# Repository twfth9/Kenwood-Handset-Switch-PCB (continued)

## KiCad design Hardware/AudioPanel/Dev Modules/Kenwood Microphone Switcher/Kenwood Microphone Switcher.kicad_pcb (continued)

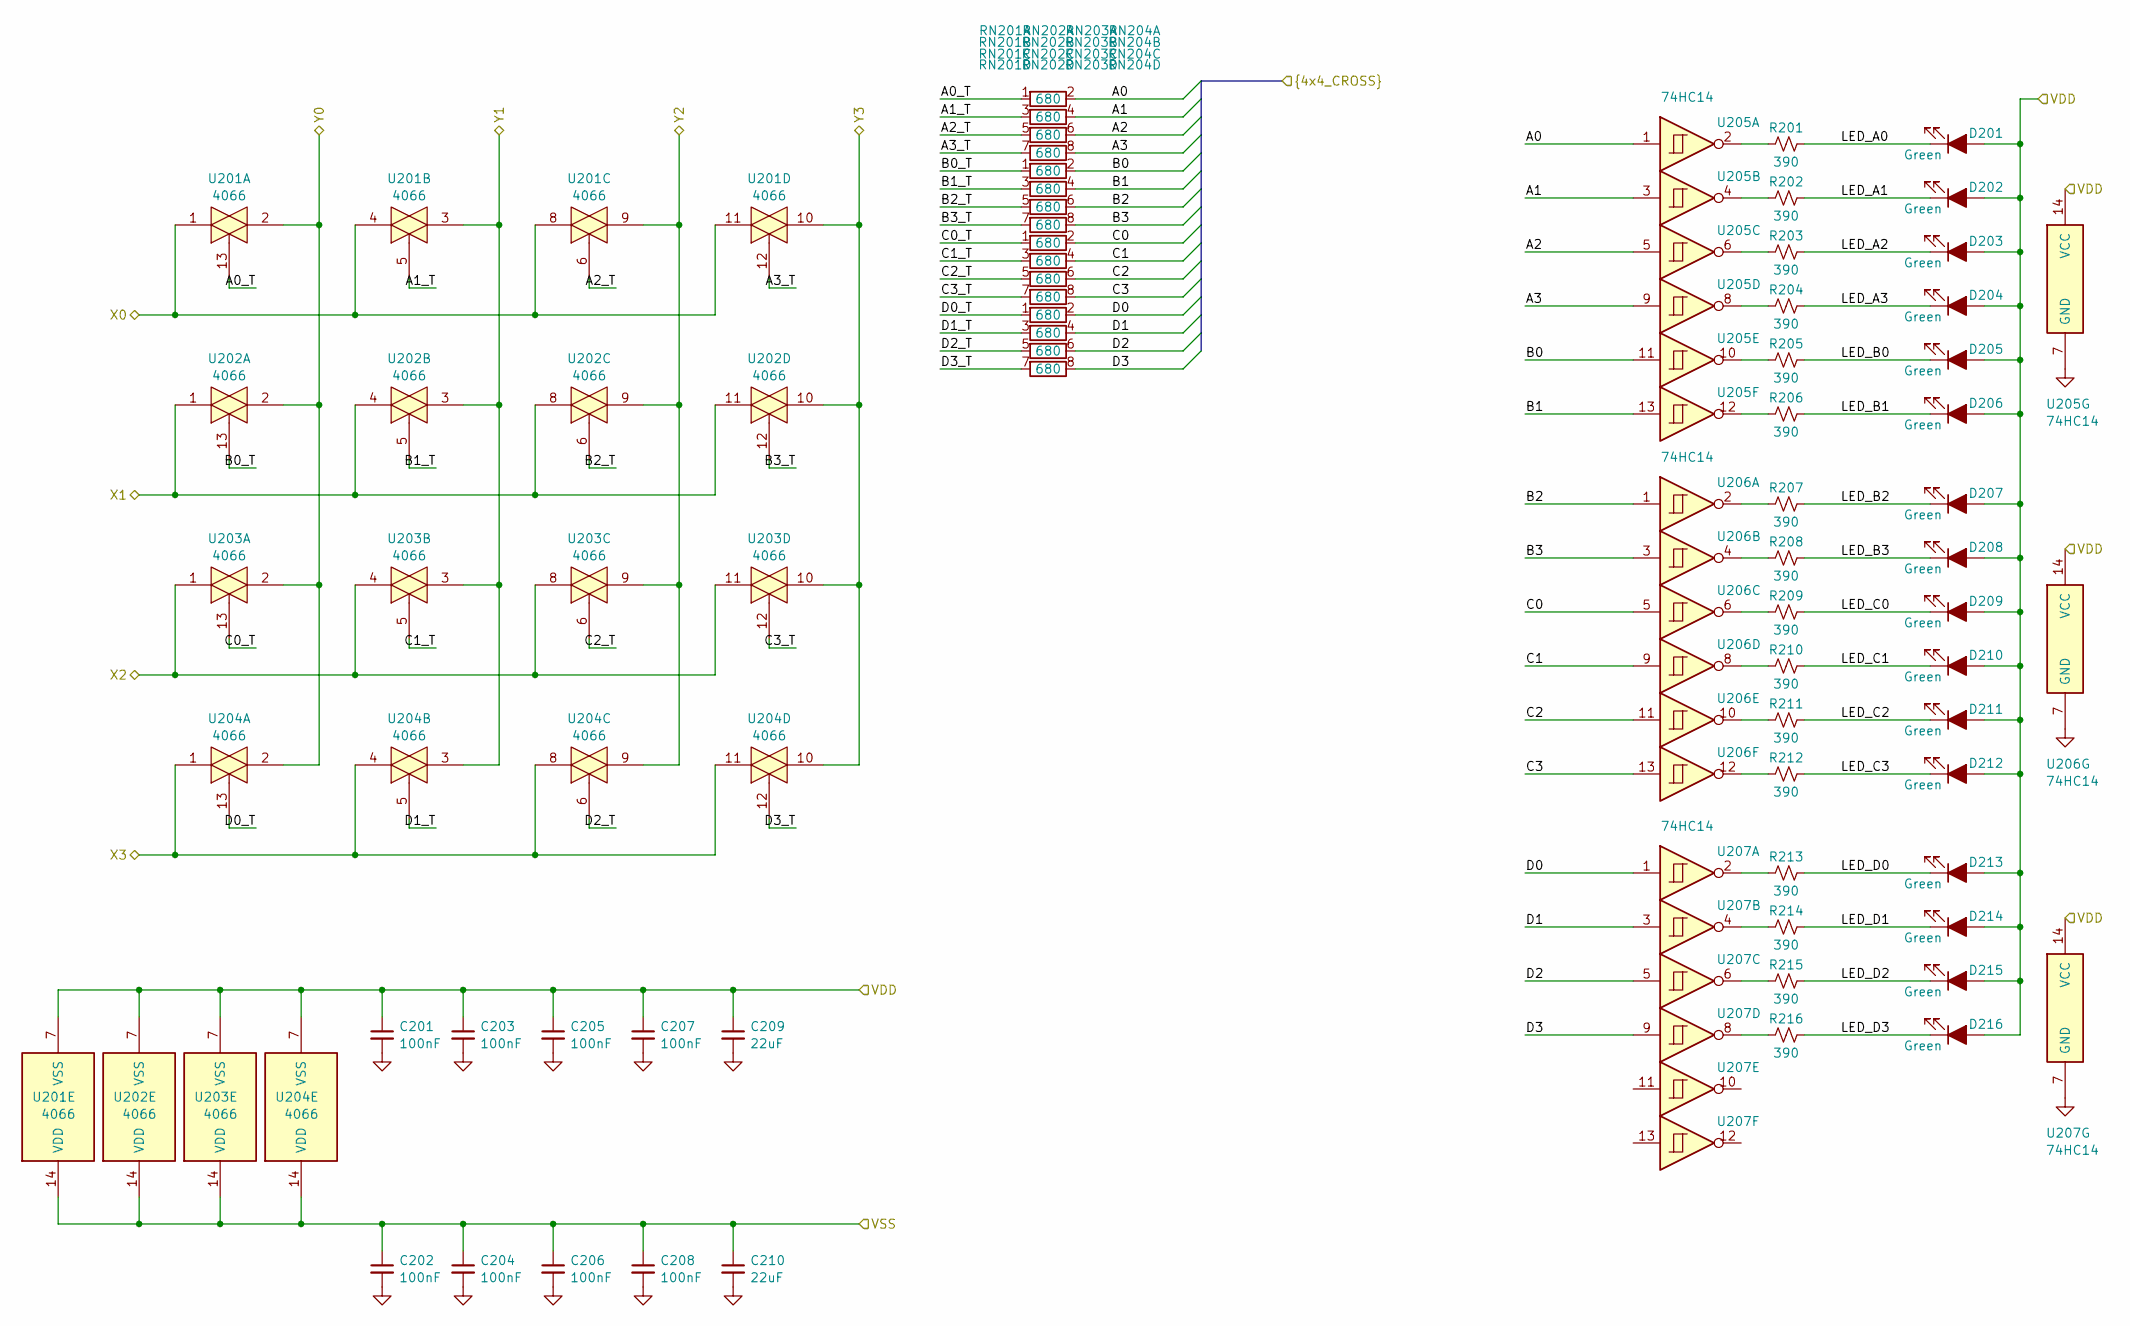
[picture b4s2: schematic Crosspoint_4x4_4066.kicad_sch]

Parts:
C201, C202, C203, C204, C205, C206, C207, C208: 100nF; C_0402_1005Metric
C209, C210: 22uF; C_0603_1608Metric
D201, D202, D203, D204, D205, D206, D207, D208, D209, D210, D211, D212, D213, D214, D215, D216: Green; LED_0603_1608Metric; DigiKey Part Number 732-5016-ND
R201, R202, R203, R204, R205, R206, R207, R208, R209, R210, R211, R212, R213, R214, R215, R216: 390; R_0402_1005Metric
RN201, RN202, RN203, RN204: 680; R_Array_Convex_4x1206
U201, U202, U203, U204: 4066; SOIC-14_3.9x8.7mm_P1.27mm
U205, U206, U207: 74HC14; SOIC-14_3.9x8.7mm_P1.27mm

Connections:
/4x4 Crosspoint Switch/A0: RN201.2, U205.1; also elsewhere on the board
/4x4 Crosspoint Switch/A0_T: RN201.1, U201.13
/4x4 Crosspoint Switch/A1: RN201.4, U205.3; also elsewhere on the board
/4x4 Crosspoint Switch/A1_T: RN201.3, U201.5
/4x4 Crosspoint Switch/A2: RN201.6, U205.5; also elsewhere on the board
/4x4 Crosspoint Switch/A2_T: RN201.5, U201.6
/4x4 Crosspoint Switch/A3: RN201.8, U205.9; also elsewhere on the board
/4x4 Crosspoint Switch/A3_T: RN201.7, U201.12
/4x4 Crosspoint Switch/B0: RN202.2, U205.11; also elsewhere on the board
/4x4 Crosspoint Switch/B0_T: RN202.1, U202.13
/4x4 Crosspoint Switch/B1: RN202.4, U205.13; also elsewhere on the board
/4x4 Crosspoint Switch/B1_T: RN202.3, U202.5
/4x4 Crosspoint Switch/B2: RN202.6, U206.1; also elsewhere on the board
/4x4 Crosspoint Switch/B2_T: RN202.5, U202.6
/4x4 Crosspoint Switch/B3: RN202.8, U206.3; also elsewhere on the board
/4x4 Crosspoint Switch/B3_T: RN202.7, U202.12
/4x4 Crosspoint Switch/C0: RN203.2, U206.5; also elsewhere on the board
/4x4 Crosspoint Switch/C0_T: RN203.1, U203.13
/4x4 Crosspoint Switch/C1: RN203.4, U206.9; also elsewhere on the board
/4x4 Crosspoint Switch/C1_T: RN203.3, U203.5
/4x4 Crosspoint Switch/C2: RN203.6, U206.11; also elsewhere on the board
/4x4 Crosspoint Switch/C2_T: RN203.5, U203.6
/4x4 Crosspoint Switch/C3: RN203.8, U206.13; also elsewhere on the board
/4x4 Crosspoint Switch/C3_T: RN203.7, U203.12
/4x4 Crosspoint Switch/D0: RN204.2, U207.1; also elsewhere on the board
/4x4 Crosspoint Switch/D0_T: RN204.1, U204.13
/4x4 Crosspoint Switch/D1: RN204.4, U207.3; also elsewhere on the board
/4x4 Crosspoint Switch/D1_T: RN204.3, U204.5
/4x4 Crosspoint Switch/D2: RN204.6, U207.5; also elsewhere on the board
/4x4 Crosspoint Switch/D2_T: RN204.5, U204.6
/4x4 Crosspoint Switch/D3: RN204.8, U207.9; also elsewhere on the board
/4x4 Crosspoint Switch/D3_T: RN204.7, U204.12
/4x4 Crosspoint Switch/LED_A0: D201.1 (K), R201.1
/4x4 Crosspoint Switch/LED_A1: D202.1 (K), R202.1
/4x4 Crosspoint Switch/LED_A2: D203.1 (K), R203.1
/4x4 Crosspoint Switch/LED_A3: D204.1 (K), R204.1
/4x4 Crosspoint Switch/LED_B0: D205.1 (K), R205.1
/4x4 Crosspoint Switch/LED_B1: D206.1 (K), R206.1
/4x4 Crosspoint Switch/LED_B2: D207.1 (K), R207.1
/4x4 Crosspoint Switch/LED_B3: D208.1 (K), R208.1
/4x4 Crosspoint Switch/LED_C0: D209.1 (K), R209.1
/4x4 Crosspoint Switch/LED_C1: D210.1 (K), R210.1
/4x4 Crosspoint Switch/LED_C2: D211.1 (K), R211.1
/4x4 Crosspoint Switch/LED_C3: D212.1 (K), R212.1
/4x4 Crosspoint Switch/LED_D0: D213.1 (K), R213.1
/4x4 Crosspoint Switch/LED_D1: D214.1 (K), R214.1
/4x4 Crosspoint Switch/LED_D2: D215.1 (K), R215.1
/4x4 Crosspoint Switch/LED_D3: D216.1 (K), R216.1
/480_MIC.MIC: U201.1, U201.4, U201.8, U201.11; also elsewhere on the board
/700_MIC.MIC: U203.1, U203.4, U203.8, U203.11; also elsewhere on the board
/710_MIC.MIC: U202.1, U202.4, U202.8, U202.11; also elsewhere on the board
/+5V_CROSSPOINT: C201.1, C203.1, C205.1, C207.1, C209.1, D201.2 (A), D202.2 (A), D203.2 (A), D204.2 (A), D205.2 (A), D206.2 (A), D207.2 (A), D208.2 (A), D209.2 (A), D210.2 (A), D211.2 (A), D212.2 (A), D213.2 (A), D214.2 (A), D215.2 (A), D216.2 (A), U201.7 (VSS), U202.7 (VSS), U203.7 (VSS), U204.7 (VSS), U205.14 (VCC), U206.14 (VCC), U207.14 (VCC); also elsewhere on the board
/CODRIVER_MIC.MIC: U201.3, U202.3, U203.3, U204.3; also elsewhere on the board
/CROSSMIC_A: U201.9, U202.9, U203.9, U204.9; also elsewhere on the board
/CROSSMIC_B: U201.10, U202.10, U203.10, U204.10; also elsewhere on the board
/DRIVER_MIC.MIC: U201.2, U202.2, U203.2, U204.2; also elsewhere on the board
/EXTRA_MIC.MIC: U204.1, U204.4, U204.8, U204.11; also elsewhere on the board
/VSS_CROSSPOINT: C202.1, C204.1, C206.1, C208.1, C210.1, U201.14 (VDD), U202.14 (VDD), U203.14 (VDD), U204.14 (VDD); also elsewhere on the board
GND: C201.2, C202.2, C203.2, C204.2, C205.2, C206.2, C207.2, C208.2, C209.2, C210.2, U205.7 (GND), U206.7 (GND), U207.7 (GND); also elsewhere on the board
unnamed: R201.2, U205.2
unnamed: R202.2, U205.4
unnamed: R203.2, U205.6
unnamed: R204.2, U205.8
unnamed: R205.2, U205.10
unnamed: R206.2, U205.12
unnamed: R207.2, U206.2
unnamed: R208.2, U206.4
unnamed: R209.2, U206.6
unnamed: R210.2, U206.8
unnamed: R211.2, U206.10
unnamed: R212.2, U206.12
unnamed: R213.2, U207.2
unnamed: R214.2, U207.4
unnamed: R215.2, U207.6
unnamed: R216.2, U207.8

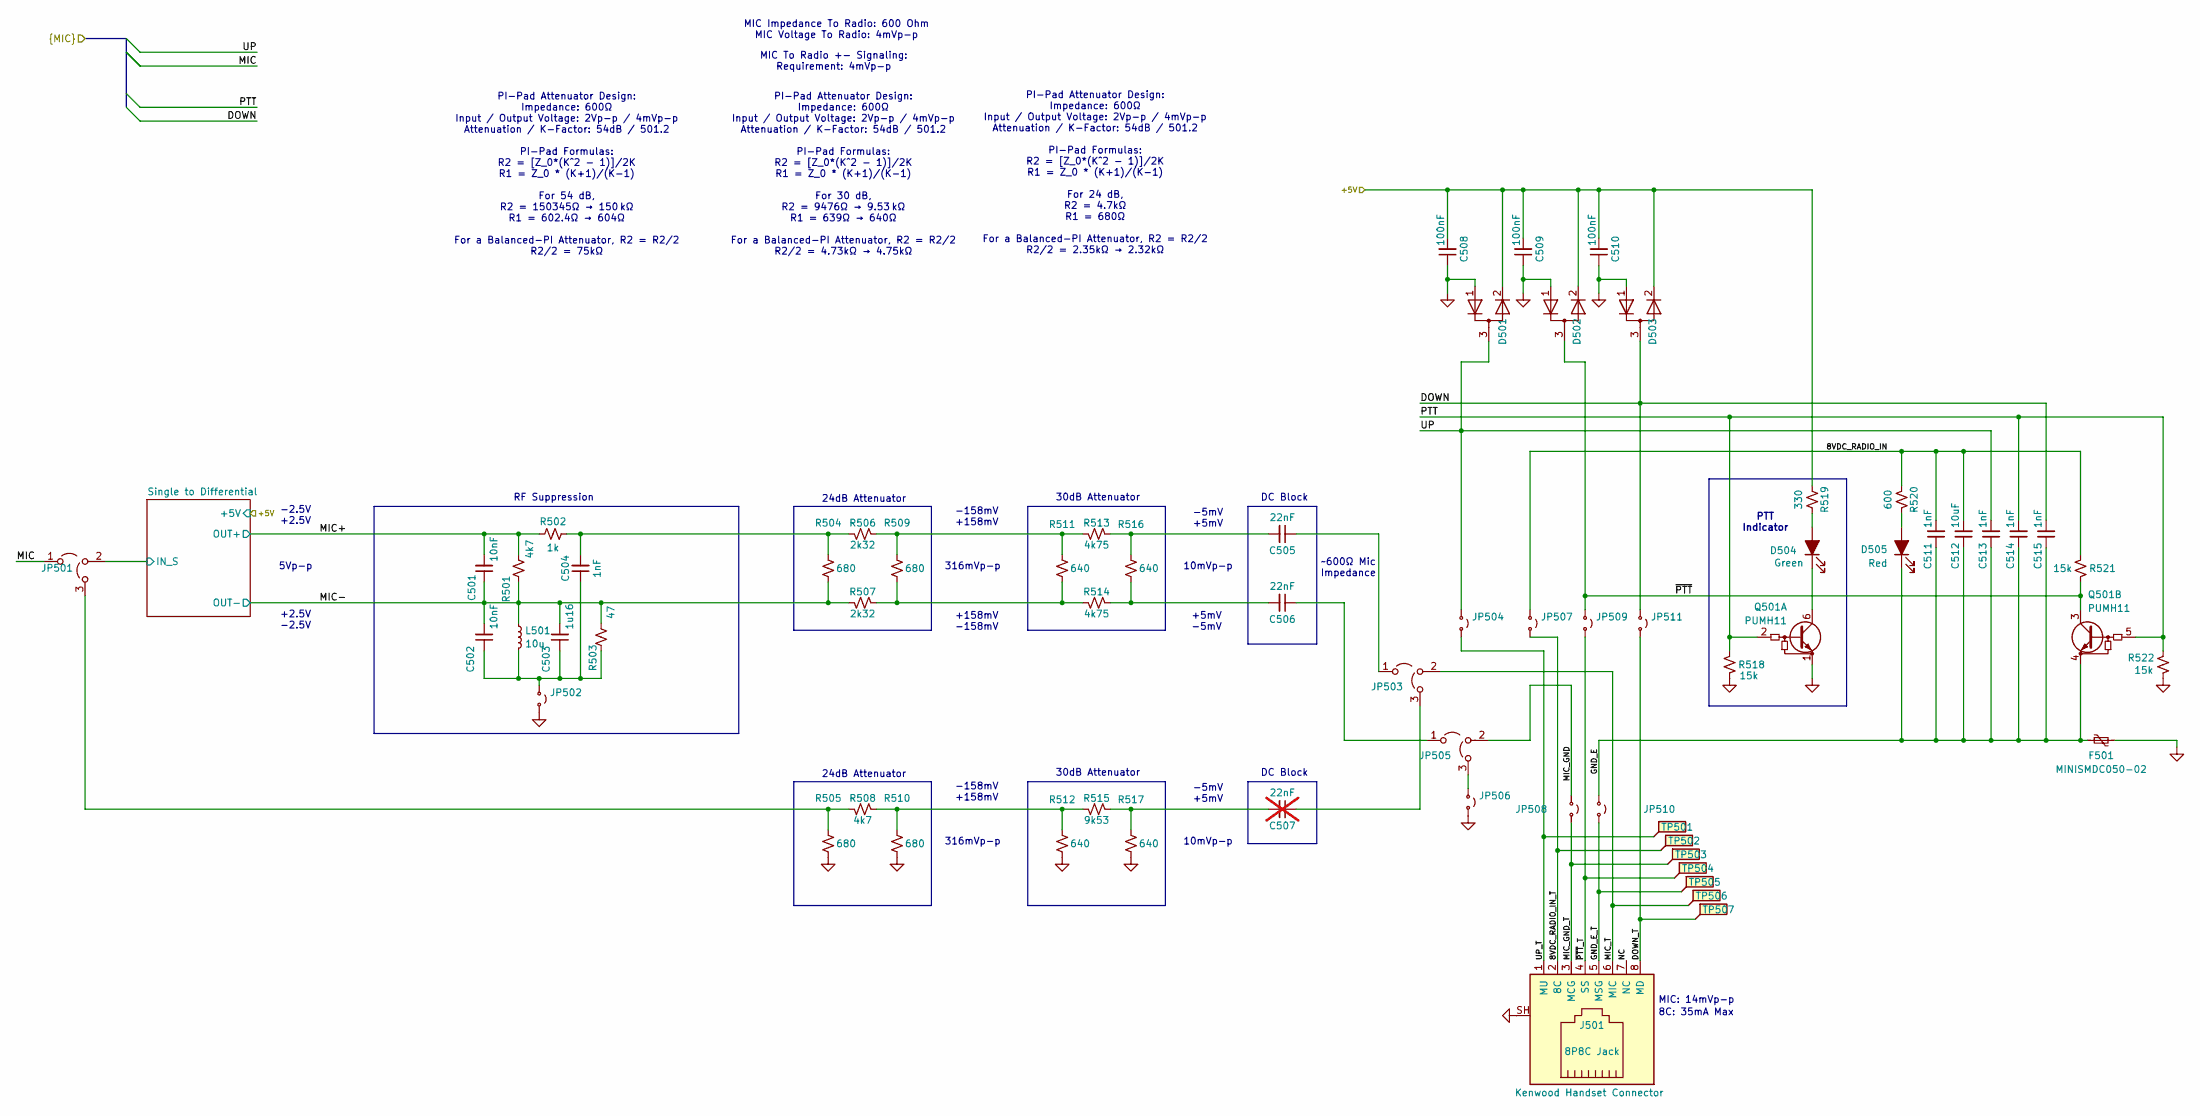
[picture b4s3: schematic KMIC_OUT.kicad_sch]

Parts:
C501, C502: 10nF; C_0402_1005Metric
C503: 1u16; C_0603_1608Metric
C504, C511, C513, C514, C515: 1nF; C_0402_1005Metric
C505, C506: 22nF; C_0402_1005Metric
C507: 22nF; C_0402_1005Metric; not fitted
C508, C509, C510: 100nF; C_0402_1005Metric
C512: 10uF; C_0603_1608Metric
D501, D502, D503: SBAV99LT1G; SOT-23
D504: Green; LED_0603_1608Metric; DigiKey Part Number 732-5016-ND
D505: Red; LED_0603_1608Metric; DigiKey Part Number 732-5016-ND
F501: MINISMDC050-02; Fuse_0805_2012Metric
J501: 8P8C Jack; Mystery_RJ45
JP501, JP503, JP505: Jumper_3_Open; SolderBridge_3L
JP502, JP504, JP506, JP507, JP508, JP509, JP510, JP511: Jumper_2_Small_Open; SolderJumper-2_P1.3mm_Open_Pad1.0x1.5mm
L501: 10u; L_0805_2012Metric
Q501: PUMH11; SOT363_NXP
R501, R508: 4k7; R_0402_1005Metric
R502: 1k; R_0402_1005Metric
R503: 47; R_0402_1005Metric
R504, R505, R509, R510: 680; R_0402_1005Metric
R506, R507: 2k32; R_0402_1005Metric
R511, R512, R516, R517: 640; R_0402_1005Metric
R513, R514: 4k75; R_0402_1005Metric
R515: 9k53; R_0402_1005Metric
R518, R521, R522: 15k; R_0402_1005Metric
R519: 330; R_0402_1005Metric
R520: 600; R_0402_1005Metric
TP501, TP502, TP503, TP504, TP505, TP506, TP507: TestPoint_Flag; KEYSTONE_5017

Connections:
/710_MIC.DOWN: C515.2, D503.3 (common), JP511.1 (A)
/710_MIC.MIC: JP501.1 (A); also elsewhere on the board
/710_MIC.PTT: C514.2, Q501.2 (B1), Q501.5 (B2), R518.1, R522.1; also elsewhere on the board
/710_MIC.UP: C513.2, D501.3 (common), JP504.1 (A); also elsewhere on the board
/+5V_MIC_710: C508.2, C509.2, C510.2, D501.2 (K), D502.2 (K), D503.2 (K), R519.2; also elsewhere on the board
/D-710 MIC Output/8VDC_RADIO_IN: C511.2, C512.2, JP507.1 (A), R520.1, R521.1
/D-710 MIC Output/8VDC_RADIO_IN_T: J501.2 (8C), JP507.2 (B), TP502.1
/D-710 MIC Output/DOWN_T: J501.8 (MD), JP511.2 (B), TP507.1
/D-710 MIC Output/GND_E: C511.1, C512.1, C513.1, C514.1, C515.1, D505.1 (K), F501.1, JP510.1 (A), Q501.4 (E2)
/D-710 MIC Output/GND_E_T: J501.5 (MSG), JP510.2 (B), TP505.1
/D-710 MIC Output/MIC+: C501.2, R501.1, R502.2; also elsewhere on the board
/D-710 MIC Output/MIC-: C501.1, C502.2, C503.2, L501.1, R501.2, R503.1, R504.2, R507.1; also elsewhere on the board
/D-710 MIC Output/MIC_GND: JP505.2 (C), JP508.1 (A)
/D-710 MIC Output/MIC_GND_T: J501.3 (MCG), JP508.2 (B), TP503.1
/D-710 MIC Output/MIC_T: J501.6 (MIC), JP503.2 (C), TP506.1
/D-710 MIC Output/NC: J501.7 (NC)
/D-710 MIC Output/Single to Differential/IN_S: JP501.2 (C); also elsewhere on the board
/D-710 MIC Output/UP_T: J501.1 (MU), JP504.2 (B), TP501.1
/D-710 MIC Output/~PTT: D502.3 (common), JP509.1 (A), Q501.3 (C2), R521.2
/D-710 MIC Output/~PTT_T: J501.4 (SS), JP509.2 (B), TP504.1
GND: C508.1, C509.1, C510.1, D501.1 (A), D502.1 (A), D503.1 (A), F501.2, J501.SH, JP502.2 (B), JP506.2 (B), Q501.1 (E1), R505.2, R510.2, R512.2, R517.2, R518.2, R522.2; also elsewhere on the board
unnamed: C504.2, R502.1, R504.1, R506.1
unnamed: C505.2, R513.2, R516.1
unnamed: C506.2, R514.2, R516.2
unnamed: C507.2, R515.2, R517.1
unnamed: D504.2 (A), R519.1
unnamed: D504.1 (K), Q501.6 (C1)
unnamed: D505.2 (A), R520.2
unnamed: JP501.3 (B), R505.1, R508.1
unnamed: C502.1, C503.1, C504.1, JP502.1 (A), L501.2, R503.2
unnamed: C505.1, JP503.1 (A)
unnamed: C507.1, JP503.3 (B)
unnamed: C506.1, JP505.1 (A)
unnamed: JP505.3 (B), JP506.1 (A)
unnamed: R506.2, R509.1, R511.1, R513.1
unnamed: R507.2, R509.2, R511.2, R514.1
unnamed: R508.2, R510.1, R512.1, R515.1

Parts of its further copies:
C601, C602, C701, C702, C801, C802: 10nF; C_0402_1005Metric
C603, C703, C803: 1u16; C_0603_1608Metric
C604, C611, C613, C614, C615, C704, C711, C713, C714, C715, C804, C811, C813, C814, C815: 1nF; C_0402_1005Metric
C605, C606, C705, C706, C805, C806: 22nF; C_0402_1005Metric
C607, C707, C807: 22nF; C_0402_1005Metric; not fitted
C608, C609, C610, C708, C709, C710, C808, C809, C810: 100nF; C_0402_1005Metric
C612, C712, C812: 10uF; C_0603_1608Metric
D601, D602, D603, D701, D702, D703, D801, D802, D803: SBAV99LT1G; SOT-23
D604, D704, D804: Green; LED_0603_1608Metric; DigiKey Part Number 732-5016-ND
D605, D705, D805: Red; LED_0603_1608Metric; DigiKey Part Number 732-5016-ND
F601, F701, F801: MINISMDC050-02; Fuse_0805_2012Metric
J601, J701, J801: 8P8C Jack; Mystery_RJ45
JP601, JP603, JP605, JP701, JP703, JP705, JP801, JP803, JP805: Jumper_3_Open; SolderBridge_3L
JP602, JP604, JP606, JP607, JP608, JP609, JP610, JP611, JP702, JP704, JP706, JP707, JP708, JP709, JP710, JP711, JP802, JP804, JP806, JP807, JP808, JP809, JP810, JP811: Jumper_2_Small_Open; SolderJumper-2_P1.3mm_Open_Pad1.0x1.5mm
L601, L701, L801: 10u; L_0805_2012Metric
Q601, Q701, Q801: PUMH11; SOT363_NXP
R601, R608, R701, R708, R801, R808: 4k7; R_0402_1005Metric
R602, R702, R802: 1k; R_0402_1005Metric
R603, R703, R803: 47; R_0402_1005Metric
R604, R605, R609, R610, R704, R705, R709, R710, R804, R805, R809, R810: 680; R_0402_1005Metric
R606, R607, R706, R707, R806, R807: 2k32; R_0402_1005Metric
R611, R612, R616, R617, R711, R712, R716, R717, R811, R812, R816, R817: 640; R_0402_1005Metric
R613, R614, R713, R714, R813, R814: 4k75; R_0402_1005Metric
R615, R715, R815: 9k53; R_0402_1005Metric
R618, R621, R622, R718, R721, R722, R818, R821, R822: 15k; R_0402_1005Metric
R619, R719, R819: 330; R_0402_1005Metric
R620, R720, R820: 600; R_0402_1005Metric
TP601, TP602, TP603, TP604, TP605, TP606, TP607, TP701, TP702, TP703, TP704, TP705, TP706, TP707, TP801, TP802, TP803, TP804, TP805, TP806, TP807: TestPoint_Flag; KEYSTONE_5017

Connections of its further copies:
/480_MIC.DOWN: C615.2, D603.3 (common), JP611.1 (A)
/480_MIC.MIC: JP601.1 (A); also elsewhere on the board
/480_MIC.PTT: C614.2, Q601.2 (B1), Q601.5 (B2), R618.1, R622.1; also elsewhere on the board
/480_MIC.UP: C613.2, D601.3 (common), JP604.1 (A); also elsewhere on the board
/700_MIC.DOWN: C715.2, D703.3 (common), JP711.1 (A)
/700_MIC.MIC: JP701.1 (A); also elsewhere on the board
/700_MIC.PTT: C714.2, Q701.2 (B1), Q701.5 (B2), R718.1, R722.1; also elsewhere on the board
/700_MIC.UP: C713.2, D701.3 (common), JP704.1 (A); also elsewhere on the board
/+5V_MIC_480: C608.2, C609.2, C610.2, D601.2 (K), D602.2 (K), D603.2 (K), R619.2; also elsewhere on the board
/+5V_MIC_700: C708.2, C709.2, C710.2, D701.2 (K), D702.2 (K), D703.2 (K), R719.2; also elsewhere on the board
/+5V_MIC_EXTRA: C808.2, C809.2, C810.2, D801.2 (K), D802.2 (K), D803.2 (K), R819.2; also elsewhere on the board
/D-700 MIC Output/8VDC_RADIO_IN: C711.2, C712.2, JP707.1 (A), R720.1, R721.1
/D-700 MIC Output/8VDC_RADIO_IN_T: J701.2 (8C), JP707.2 (B), TP702.1
/D-700 MIC Output/DOWN_T: J701.8 (MD), JP711.2 (B), TP707.1
/D-700 MIC Output/GND_E: C711.1, C712.1, C713.1, C714.1, C715.1, D705.1 (K), F701.1, JP710.1 (A), Q701.4 (E2)
/D-700 MIC Output/GND_E_T: J701.5 (MSG), JP710.2 (B), TP705.1
/D-700 MIC Output/MIC+: C701.2, R701.1, R702.2; also elsewhere on the board
/D-700 MIC Output/MIC-: C701.1, C702.2, C703.2, L701.1, R701.2, R703.1, R704.2, R707.1; also elsewhere on the board
/D-700 MIC Output/MIC_GND: JP705.2 (C), JP708.1 (A)
/D-700 MIC Output/MIC_GND_T: J701.3 (MCG), JP708.2 (B), TP703.1
/D-700 MIC Output/MIC_T: J701.6 (MIC), JP703.2 (C), TP706.1
/D-700 MIC Output/NC: J701.7 (NC)
/D-700 MIC Output/Single to Differential/IN_S: JP701.2 (C); also elsewhere on the board
/D-700 MIC Output/UP_T: J701.1 (MU), JP704.2 (B), TP701.1
/D-700 MIC Output/~PTT: D702.3 (common), JP709.1 (A), Q701.3 (C2), R721.2
/D-700 MIC Output/~PTT_T: J701.4 (SS), JP709.2 (B), TP704.1
/EXTRA MIC Output/8VDC_RADIO_IN: C811.2, C812.2, JP807.1 (A), R820.1, R821.1
/EXTRA MIC Output/8VDC_RADIO_IN_T: J801.2 (8C), JP807.2 (B), TP802.1
/EXTRA MIC Output/DOWN_T: J801.8 (MD), JP811.2 (B), TP807.1
/EXTRA MIC Output/GND_E: C811.1, C812.1, C813.1, C814.1, C815.1, D805.1 (K), F801.1, JP810.1 (A), Q801.4 (E2)
/EXTRA MIC Output/GND_E_T: J801.5 (MSG), JP810.2 (B), TP805.1
/EXTRA MIC Output/MIC+: C801.2, R801.1, R802.2; also elsewhere on the board
/EXTRA MIC Output/MIC-: C801.1, C802.2, C803.2, L801.1, R801.2, R803.1, R804.2, R807.1; also elsewhere on the board
/EXTRA MIC Output/MIC_GND: JP805.2 (C), JP808.1 (A)
/EXTRA MIC Output/MIC_GND_T: J801.3 (MCG), JP808.2 (B), TP803.1
/EXTRA MIC Output/MIC_T: J801.6 (MIC), JP803.2 (C), TP806.1
/EXTRA MIC Output/NC: J801.7 (NC)
/EXTRA MIC Output/Single to Differential/IN_S: JP801.2 (C); also elsewhere on the board
/EXTRA MIC Output/UP_T: J801.1 (MU), JP804.2 (B), TP801.1
/EXTRA MIC Output/~PTT: D802.3 (common), JP809.1 (A), Q801.3 (C2), R821.2
/EXTRA MIC Output/~PTT_T: J801.4 (SS), JP809.2 (B), TP804.1
/EXTRA_MIC.DOWN: C815.2, D803.3 (common), JP811.1 (A)
/EXTRA_MIC.MIC: JP801.1 (A); also elsewhere on the board
/EXTRA_MIC.PTT: C814.2, Q801.2 (B1), Q801.5 (B2), R818.1, R822.1; also elsewhere on the board
/EXTRA_MIC.UP: C813.2, D801.3 (common), JP804.1 (A); also elsewhere on the board
/TS-480 MIC Output/8VDC_RADIO_IN: C611.2, C612.2, JP607.1 (A), R620.1, R621.1
/TS-480 MIC Output/8VDC_RADIO_IN_T: J601.2 (8C), JP607.2 (B), TP602.1
/TS-480 MIC Output/DOWN_T: J601.8 (MD), JP611.2 (B), TP607.1
/TS-480 MIC Output/GND_E: C611.1, C612.1, C613.1, C614.1, C615.1, D605.1 (K), F601.1, JP610.1 (A), Q601.4 (E2)
/TS-480 MIC Output/GND_E_T: J601.5 (MSG), JP610.2 (B), TP605.1
/TS-480 MIC Output/MIC+: C601.2, R601.1, R602.2; also elsewhere on the board
/TS-480 MIC Output/MIC-: C601.1, C602.2, C603.2, L601.1, R601.2, R603.1, R604.2, R607.1; also elsewhere on the board
/TS-480 MIC Output/MIC_GND: JP605.2 (C), JP608.1 (A)
/TS-480 MIC Output/MIC_GND_T: J601.3 (MCG), JP608.2 (B), TP603.1
/TS-480 MIC Output/MIC_T: J601.6 (MIC), JP603.2 (C), TP606.1
/TS-480 MIC Output/NC: J601.7 (NC)
/TS-480 MIC Output/Single to Differential/IN_S: JP601.2 (C); also elsewhere on the board
/TS-480 MIC Output/UP_T: J601.1 (MU), JP604.2 (B), TP601.1
/TS-480 MIC Output/~PTT: D602.3 (common), JP609.1 (A), Q601.3 (C2), R621.2
/TS-480 MIC Output/~PTT_T: J601.4 (SS), JP609.2 (B), TP604.1
GND: C608.1, C609.1, C610.1, C708.1, C709.1, C710.1, C808.1, C809.1, C810.1, D601.1 (A), D602.1 (A), D603.1 (A), D701.1 (A), D702.1 (A), D703.1 (A), D801.1 (A), D802.1 (A), D803.1 (A), F601.2, F701.2, F801.2, J601.SH, J701.SH, J801.SH, JP602.2 (B), JP606.2 (B), JP702.2 (B), JP706.2 (B), JP802.2 (B), JP806.2 (B), Q601.1 (E1), Q701.1 (E1), Q801.1 (E1), R605.2, R610.2, R612.2, R617.2, R618.2, R622.2, R705.2, R710.2, R712.2, R717.2, R718.2, R722.2, R805.2, R810.2, R812.2, R817.2, R818.2, R822.2; also elsewhere on the board
unnamed: C604.2, R602.1, R604.1, R606.1
unnamed: C605.2, R613.2, R616.1
unnamed: C606.2, R614.2, R616.2
unnamed: C607.2, R615.2, R617.1
unnamed: C704.2, R702.1, R704.1, R706.1
unnamed: C705.2, R713.2, R716.1
unnamed: C706.2, R714.2, R716.2
unnamed: C707.2, R715.2, R717.1
unnamed: C804.2, R802.1, R804.1, R806.1
unnamed: C805.2, R813.2, R816.1
unnamed: C806.2, R814.2, R816.2
unnamed: C807.2, R815.2, R817.1
unnamed: D604.2 (A), R619.1
unnamed: D604.1 (K), Q601.6 (C1)
unnamed: D605.2 (A), R620.2
unnamed: D704.2 (A), R719.1
unnamed: D704.1 (K), Q701.6 (C1)
unnamed: D705.2 (A), R720.2
unnamed: D804.2 (A), R819.1
unnamed: D804.1 (K), Q801.6 (C1)
unnamed: D805.2 (A), R820.2
unnamed: JP601.3 (B), R605.1, R608.1
unnamed: C602.1, C603.1, C604.1, JP602.1 (A), L601.2, R603.2
unnamed: C605.1, JP603.1 (A)
unnamed: C607.1, JP603.3 (B)
unnamed: C606.1, JP605.1 (A)
unnamed: JP605.3 (B), JP606.1 (A)
unnamed: JP701.3 (B), R705.1, R708.1
unnamed: C702.1, C703.1, C704.1, JP702.1 (A), L701.2, R703.2
unnamed: C705.1, JP703.1 (A)
unnamed: C707.1, JP703.3 (B)
unnamed: C706.1, JP705.1 (A)
unnamed: JP705.3 (B), JP706.1 (A)
unnamed: JP801.3 (B), R805.1, R808.1
unnamed: C802.1, C803.1, C804.1, JP802.1 (A), L801.2, R803.2
unnamed: C805.1, JP803.1 (A)
unnamed: C807.1, JP803.3 (B)
unnamed: C806.1, JP805.1 (A)
unnamed: JP805.3 (B), JP806.1 (A)
unnamed: R606.2, R609.1, R611.1, R613.1
unnamed: R607.2, R609.2, R611.2, R614.1
unnamed: R608.2, R610.1, R612.1, R615.1
unnamed: R706.2, R709.1, R711.1, R713.1
unnamed: R707.2, R709.2, R711.2, R714.1
unnamed: R708.2, R710.1, R712.1, R715.1
unnamed: R806.2, R809.1, R811.1, R813.1
unnamed: R807.2, R809.2, R811.2, R814.1
unnamed: R808.2, R810.1, R812.1, R815.1

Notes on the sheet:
30dB Attenuator
PI-Pad Attenuator Design: Impedance: 600Ω Input / Output Voltage: 2Vp-p / 4mVp-p Attenuation / K-Factor: 54dB / 501.2 PI-Pad Formulas: R2 = [Z_0*(K^2 - 1)]/2K R1 = Z_0 * (K+1)/(K-1) For 54 dB, R2 = 150345Ω → 150 kΩ R1 = 602.4Ω → 604Ω For a Balanced-PI Attenuator, R2 = R2/2 R2/2 = 75kΩ
-5mV +5mV
PI-Pad Attenuator Design: Impedance: 600Ω Input / Output Voltage: 2Vp-p / 4mVp-p Attenuation / K-Factor: 54dB / 501.2 PI-Pad Formulas: R2 = [Z_0*(K^2 - 1)]/2K R1 = Z_0 * (K+1)/(K-1) For 24 dB, R2 = 4.7kΩ R1 = 680Ω For a Balanced-PI Attenuator, R2 = R2/2 R2/2 = 2.35kΩ → 2.32kΩ
RF Suppression
10mVp-p
316mVp-p
DC Block
MIC Impedance To Radio: 600 Ohm MIC Voltage To Radio: 4mVp-p
-2.5V +2.5V
24dB Attenuator
~600Ω Mic Impedance
PTT Indicator
MIC: 14mVp-p
+158mV -158mV
8C: 35mA Max
PI-Pad Attenuator Design: Impedance: 600Ω Input / Output Voltage: 2Vp-p / 4mVp-p Attenuation / K-Factor: 54dB / 501.2 PI-Pad Formulas: R2 = [Z_0*(K^2 - 1)]/2K R1 = Z_0 * (K+1)/(K-1) For 30 dB, R2 = 9476Ω → 9.53 kΩ R1 = 639Ω → 640Ω For a Balanced-PI Attenuator, R2 = R2/2 R2/2 = 4.73kΩ → 4.75kΩ
-158mV +158mV
MIC To Radio +- Signaling: Requirement: 4mVp-p
+2.5V -2.5V
5Vp-p
+5mV -5mV
